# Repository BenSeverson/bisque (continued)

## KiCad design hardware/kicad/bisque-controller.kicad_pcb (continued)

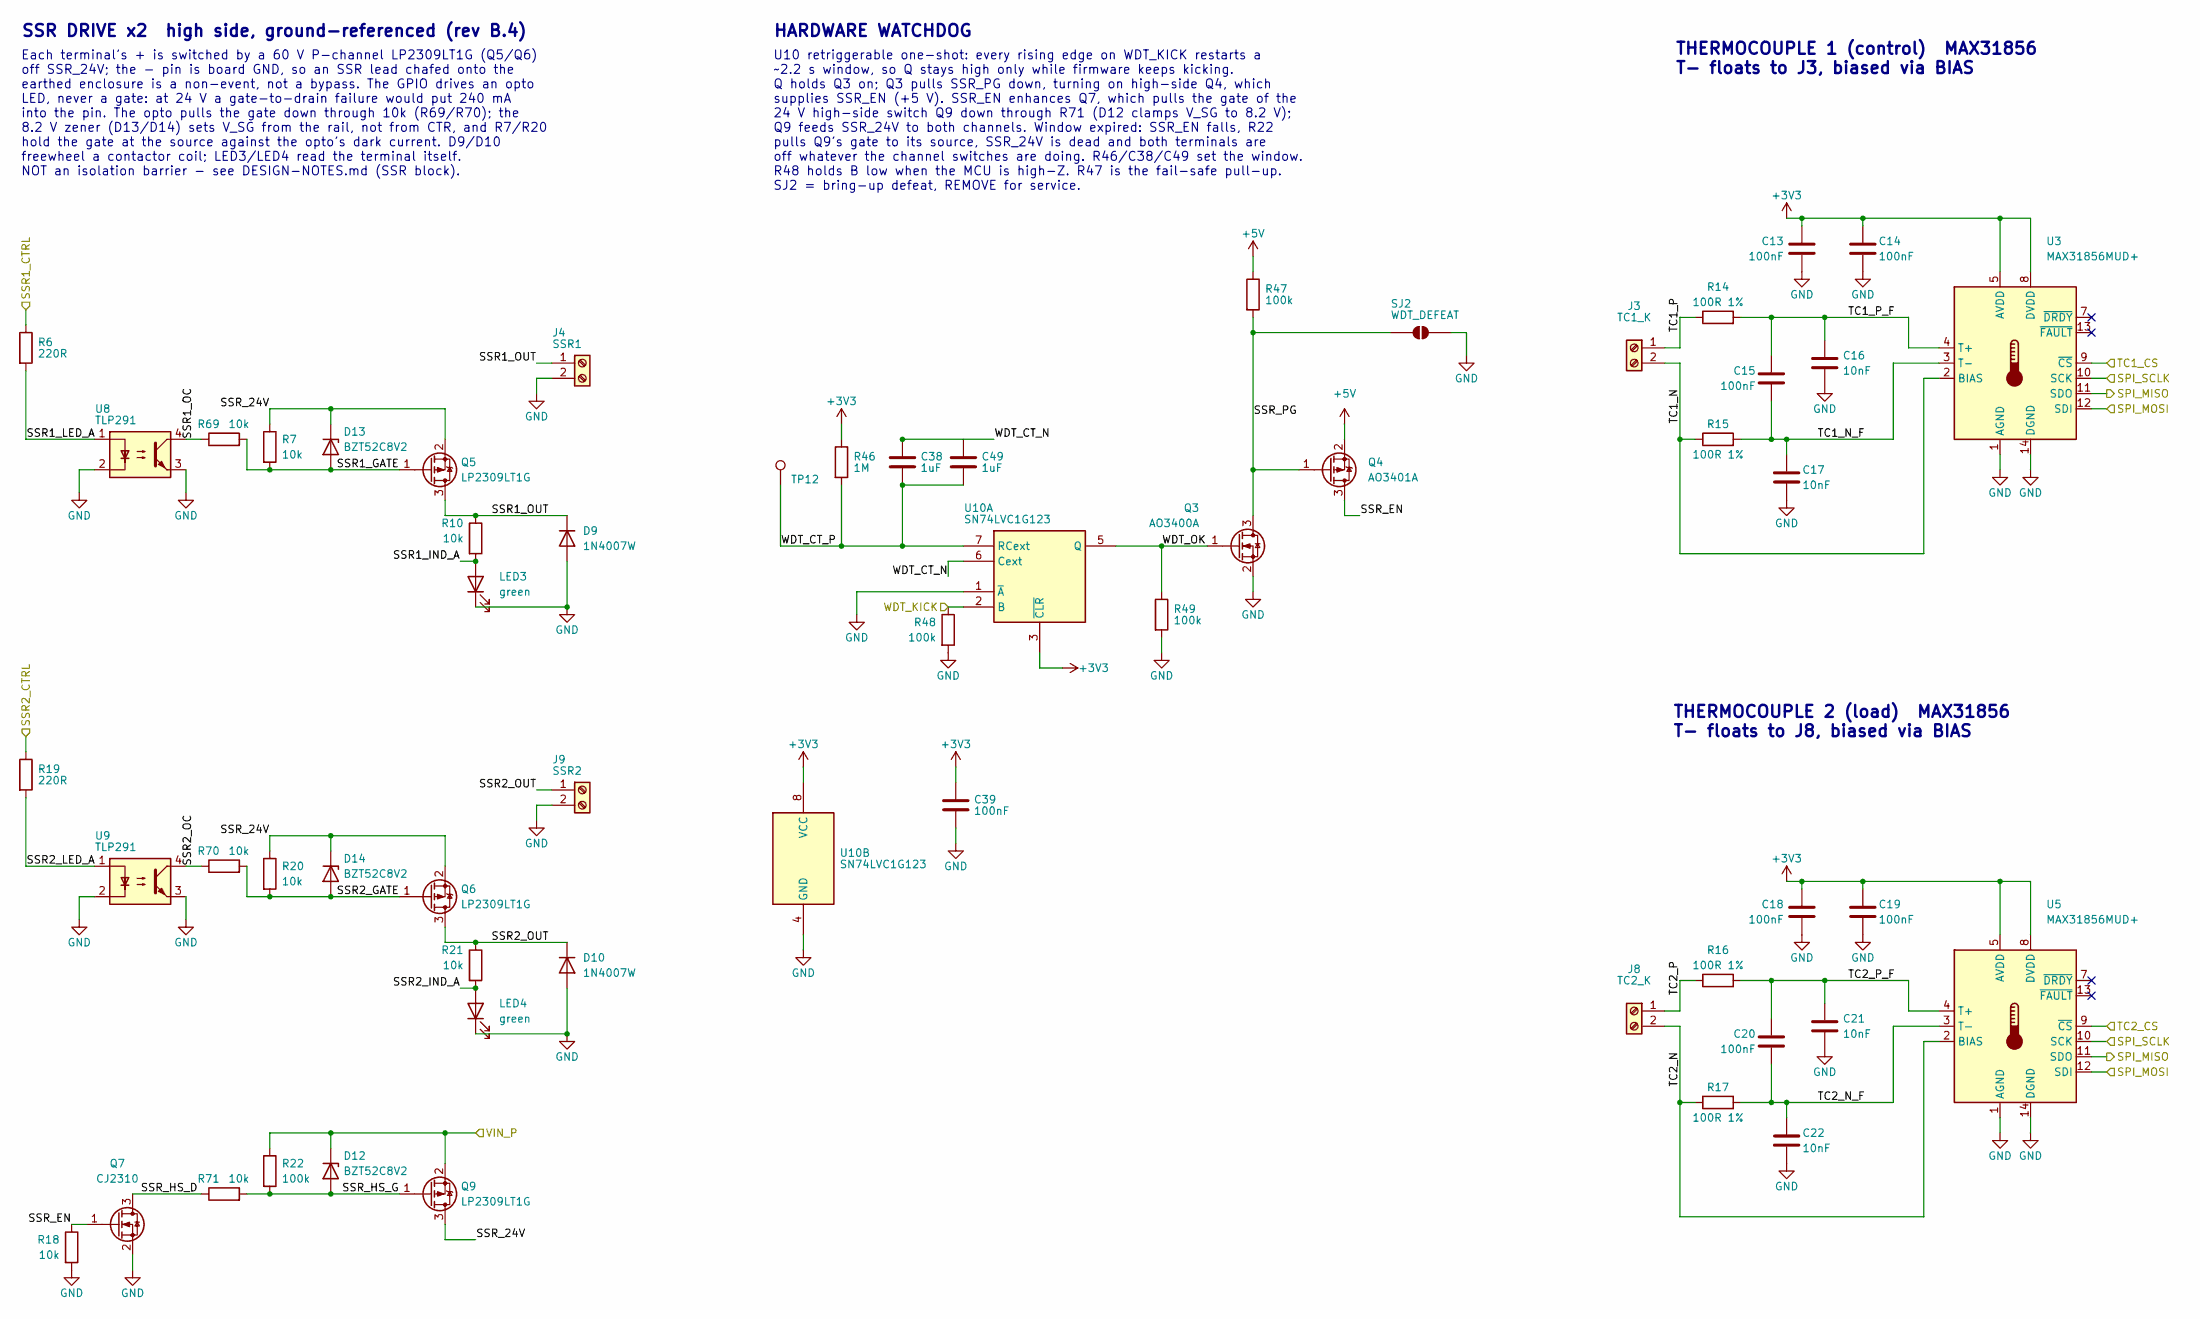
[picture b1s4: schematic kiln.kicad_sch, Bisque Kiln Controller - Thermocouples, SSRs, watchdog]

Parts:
C13, C14, C15, C18, C19, C20, C39: 100nF; C_0603_1608Metric; MPN CC0603KRX7R9BB104; LCSC C14663
C16, C17, C21, C22: 10nF; C_0805_2012Metric; MPN CL21B103KBANNNC; LCSC C1710
C38, C49: 1uF; C_0805_2012Metric; MPN CL21B105KBFNNNE; LCSC C28323
D9, D10: 1N4007W; D_SOD-123; MPN 1N4007W; LCSC C3018540
D12, D13, D14: BZT52C8V2; D_SOD-323; MPN BZT52C8V2S; LCSC C22375294
J3: TC1_K; TerminalBlock_Phoenix_MKDS-1,5-2-5.08_1x02_P5.08mm_Horizont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; MPN WJ500V-5.08-2P; LCSC C8465
J4: SSR1; TerminalBlock_Phoenix_MKDS-1,5-2-5.08_1x02_P5.08mm_Horizont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; MPN WJ500V-5.08-2P; LCSC C8465
J8: TC2_K; TerminalBlock_Phoenix_MKDS-1,5-2-5.08_1x02_P5.08mm_Horizont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; MPN WJ500V-5.08-2P; LCSC C8465
J9: SSR2; TerminalBlock_Phoenix_MKDS-1,5-2-5.08_1x02_P5.08mm_Horizont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; MPN WJ500V-5.08-2P; LCSC C8465
LED3, LED4: green; LED_0805_2012Metric; MPN KT-0805G; LCSC C2297
Q3: AO3400A; SOT-23; MPN AO3400A; LCSC C20917
Q4: AO3401A; SOT-23; MPN AO3401A; LCSC C15127
Q5, Q6, Q9: LP2309LT1G; SOT-23; MPN LP2309LT1G; LCSC C383253
Q7: CJ2310; SOT-23; MPN CJ2310; LCSC C75882
R6, R19: 220R; R_0805_2012Metric; MPN 0805W8F2200T5E; LCSC C17557
R7, R10, R18, R20, R21, R69, R70, R71: 10k; R_0805_2012Metric; MPN 0805W8F1002T5E; LCSC C17414
R14, R15, R16, R17: 100R 1%; R_0805_2012Metric; MPN 0805W8F1000T5E; LCSC C17408
R22, R47, R48, R49: 100k; R_0805_2012Metric; MPN 0805W8F1003T5E; LCSC C149504
R46: 1M; R_0805_2012Metric; MPN 0805W8F1004T5E; LCSC C17514
SJ2: WDT_DEFEAT; SolderJumper-2_P1.3mm_Open_RoundedPad1.0x1.5mm
TP12: WDT_CT_P; TestPoint_Pad_D1.0mm
U3, U5: MAX31856MUD+; TSSOP-14_4.4x5mm_P0.65mm; MPN MAX31856MUD+T; LCSC C2653162
U8, U9: TLP291; SOP-4_4.4x2.6mm_P1.27mm; MPN TLP291(GB-TP,SE; LCSC C55144
U10: SN74LVC1G123; SSOP-8_2.95x2.8mm_P0.65mm; MPN SN74LVC1G123DCTR; LCSC C123302

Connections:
+3V3: C13.1, C14.1, C18.1, C19.1, C39.1, R46.1, U3.5 (AVDD), U3.8 (DVDD), U5.5 (AVDD), U5.8 (DVDD), U10.3 (~CLR), U10.8 (VCC); also elsewhere on the board
+5V: Q4.2 (S), R47.1; also elsewhere on the board
GND: C13.2, C14.2, C16.2, C17.2, C18.2, C19.2, C21.2, C22.2, C39.2, D9.2 (A), D10.2 (A), J4.2, J9.2, LED3.1 (K), LED4.1 (K), Q3.2 (S), Q7.2 (S), R18.2, R48.2, R49.2, SJ2.2 (B), U3.1 (AGND), U3.14 (DGND), U5.1 (AGND), U5.14 (DGND), U8.2, U8.3, U9.2, U9.3, U10.1 (~A), U10.4 (GND); also elsewhere on the board
SPI_MISO: U3.11 (SDO), U5.11 (SDO); also elsewhere on the board
SPI_MOSI: U3.12 (SDI), U5.12 (SDI); also elsewhere on the board
SPI_SCLK: U3.10 (SCK), U5.10 (SCK); also elsewhere on the board
SSR1_CTRL: R6.1; also elsewhere on the board
SSR1_GATE: D13.2 (A), Q5.1 (G), R7.2, R69.2
SSR1_IND_A: LED3.2 (A), R10.2
SSR1_LED_A: R6.2, U8.1
SSR1_OC: R69.1, U8.4
SSR1_OUT: D9.1 (K), J4.1, Q5.3 (D), R10.1
SSR2_CTRL: R19.1; also elsewhere on the board
SSR2_GATE: D14.2 (A), Q6.1 (G), R20.2, R70.2
SSR2_IND_A: LED4.2 (A), R21.2
SSR2_LED_A: R19.2, U9.1
SSR2_OC: R70.1, U9.4
SSR2_OUT: D10.1 (K), J9.1, Q6.3 (D), R21.1
SSR_24V: D13.1 (K), D14.1 (K), Q5.2 (S), Q6.2 (S), Q9.3 (D), R7.1, R20.1
SSR_EN: Q4.3 (D), Q7.1 (G), R18.1
SSR_HS_D: Q7.3 (D), R71.1
SSR_HS_G: D12.2 (A), Q9.1 (G), R22.2, R71.2
SSR_PG: Q3.3 (D), Q4.1 (G), R47.2, SJ2.1 (A)
TC1_CS: U3.9 (~CS); also elsewhere on the board
TC1_N: J3.2, R15.1, U3.2 (BIAS)
TC1_N_F: C15.2, C17.1, R15.2, U3.3 (T-)
TC1_P: J3.1, R14.1
TC1_P_F: C15.1, C16.1, R14.2, U3.4 (T+)
TC2_CS: U5.9 (~CS); also elsewhere on the board
TC2_N: J8.2, R17.1, U5.2 (BIAS)
TC2_N_F: C20.2, C22.1, R17.2, U5.3 (T-)
TC2_P: J8.1, R16.1
TC2_P_F: C20.1, C21.1, R16.2, U5.4 (T+)
VIN_P: D12.1 (K), Q9.2 (S), R22.1; also elsewhere on the board
WDT_CT_N: C38.1, C49.1, U10.6 (Cext)
WDT_CT_P: C38.2, C49.2, R46.2, TP12.1, U10.7 (RCext)
WDT_KICK: R48.1, U10.2 (B); also elsewhere on the board
WDT_OK: Q3.1 (G), R49.1, U10.5 (Q)

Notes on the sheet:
SSR DRIVE x2 high side, ground-referenced (rev B.4)
Each terminal's + is switched by a 60 V P-channel LP2309LT1G (Q5/Q6) off SSR_24V; the - pin is board GND, so an SSR lead chafed onto the earthed enclosure is a non-event, not a bypass. The GPIO drives an opto LED, never a gate: at 24 V a gate-to-drain failure would put 240 mA into the pin. The opto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
HARDWARE WATCHDOG
U10 retriggerable one-shot: every rising edge on WDT_KICK restarts a ~2.2 s window, so Q stays high only while firmware keeps kicking. Q holds Q3 on; Q3 pulls SSR_PG down, turning on high-side Q4, which supplies SSR_EN (+5 V). SSR_EN enhances Q7, which pulls the gate of the 24 V high-side switch Q9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
THERMOCOUPLE 1 (control) MAX31856 T- floats to J3, biased via BIAS
THERMOCOUPLE 2 (load) MAX31856 T- floats to J8, biased via BIAS

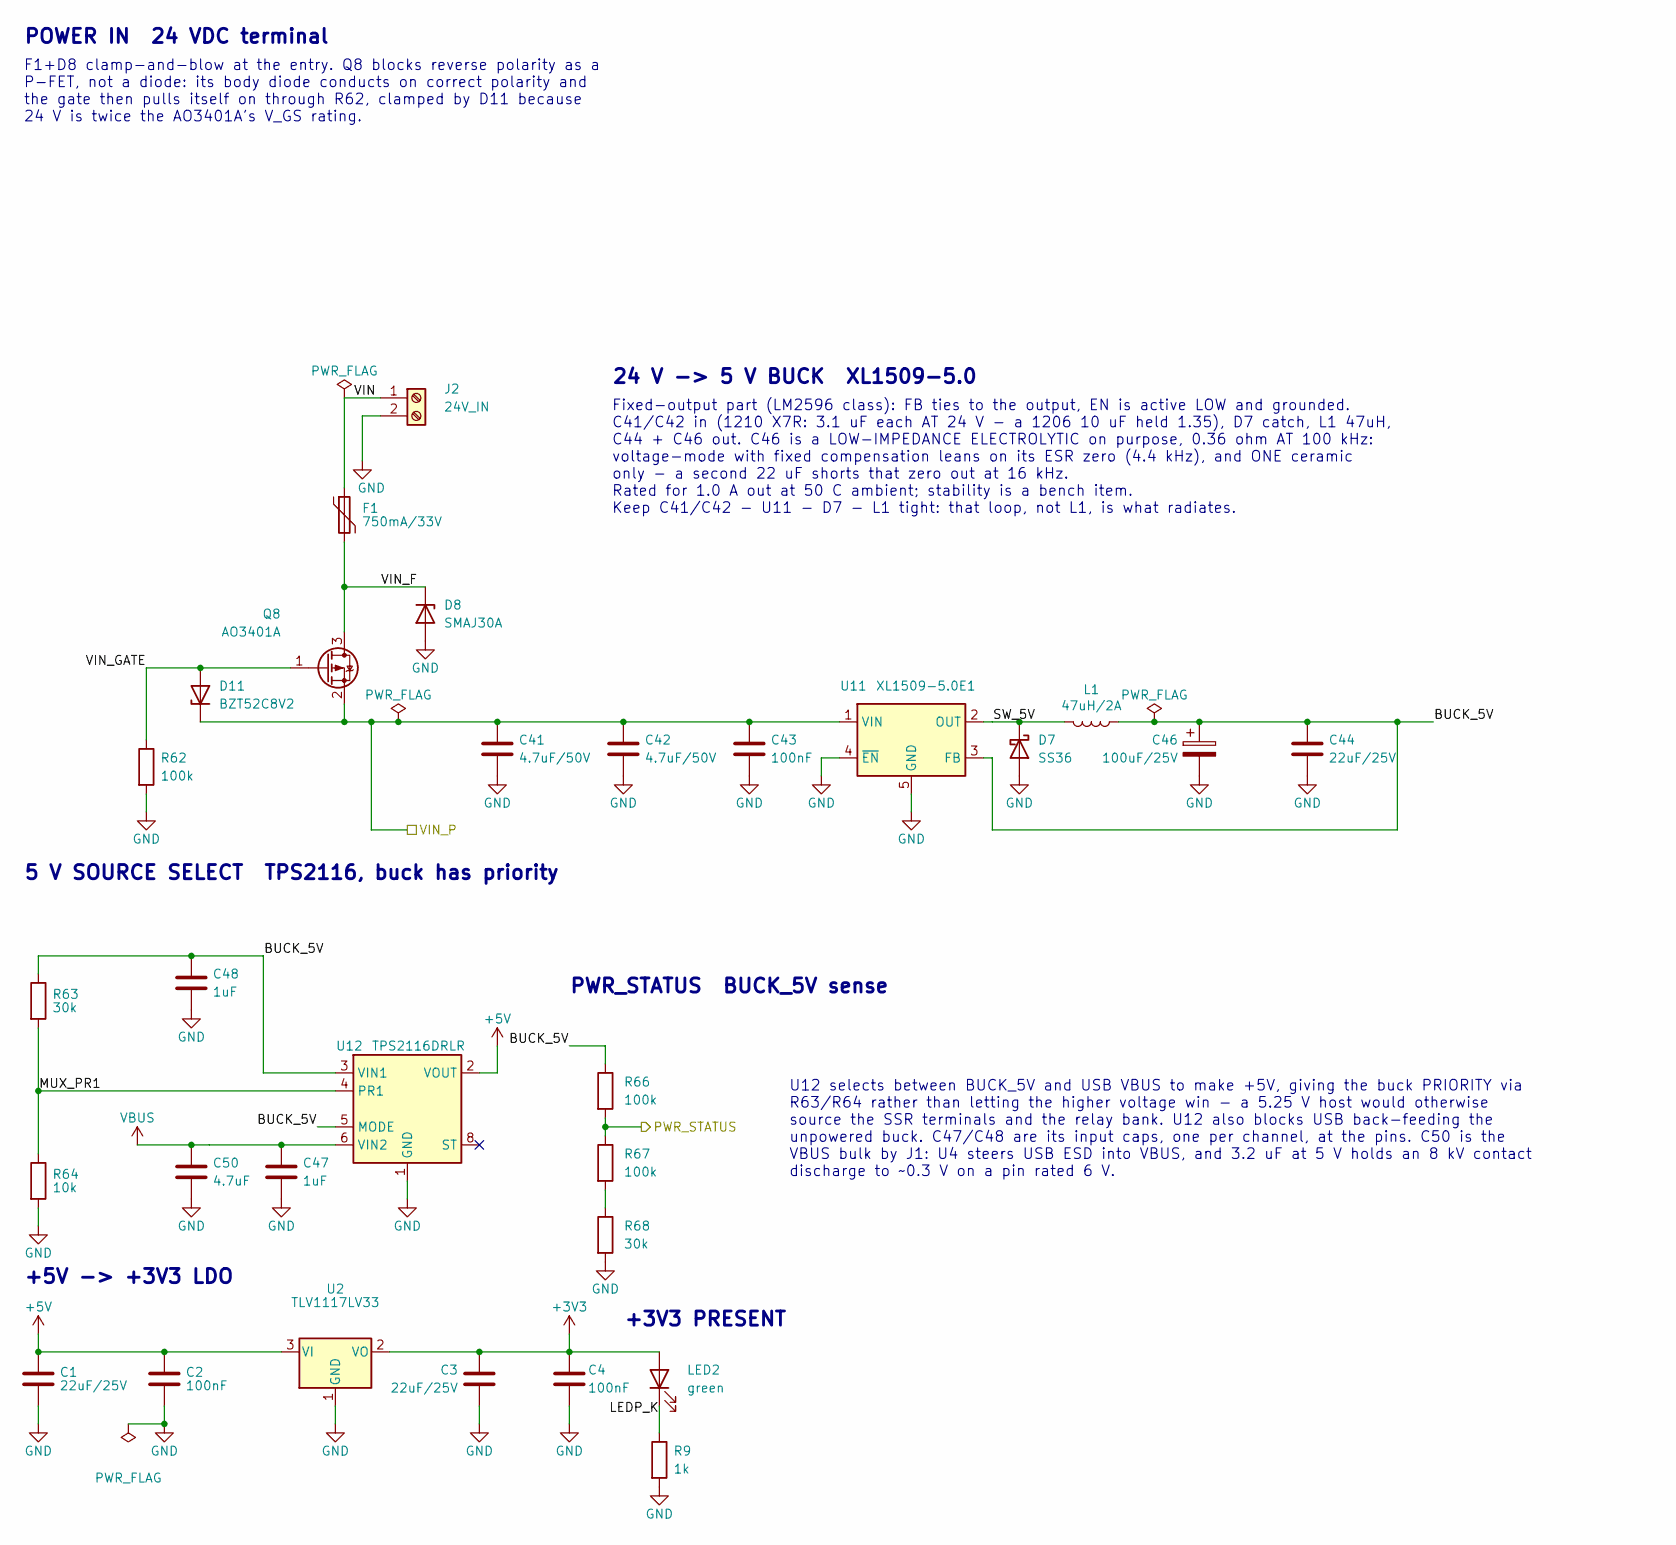
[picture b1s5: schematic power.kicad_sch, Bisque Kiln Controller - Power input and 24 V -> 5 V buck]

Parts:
C1, C3, C44: 22uF/25V; C_1206_3216Metric; MPN CL31A226KAHNNNE; LCSC C12891
C2, C4, C43: 100nF; C_0603_1608Metric; MPN CC0603KRX7R9BB104; LCSC C14663
C41, C42: 4.7uF/50V; C_1210_3225Metric; MPN CL32B475KBUYNNE; LCSC C170099
C46: 100uF/25V; CP_Elec_6.3x5.8; MPN EEEFK1E101SP; LCSC C178540
C47, C48: 1uF; C_0402_1005Metric; MPN CL05A105KA5NQNC; LCSC C52923
C50: 4.7uF; C_0805_2012Metric; MPN CL21A475KAQNNNE; LCSC C1779
D7: SS36; D_SMA; MPN SS36; LCSC C7420367
D8: SMAJ30A; D_SMA; MPN SMAJ30A; LCSC C19077547
D11: BZT52C8V2; D_SOD-323; MPN BZT52C8V2S; LCSC C22375294
F1: 750mA/33V; Fuse_1812_4532Metric; MPN JK-mSMD075-33; LCSC C369169
J2: 24V_IN; TerminalBlock_Phoenix_MKDS-1,5-2-5.08_1x02_P5.08mm_Horizont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; MPN WJ500V-5.08-2P; LCSC C8465
L1: 47uH/2A; L_Changjiang_FXL0650; MPN FXL0650-470-M; LCSC C475527
LED2: green; LED_0805_2012Metric; MPN KT-0805G; LCSC C2297
Q8: AO3401A; SOT-23; MPN AO3401A; LCSC C15127
R9: 1k; R_0805_2012Metric; MPN 0805W8F1001T5E; LCSC C17513
R62, R66, R67: 100k; R_0805_2012Metric; MPN 0805W8F1003T5E; LCSC C149504
R63, R68: 30k; R_0805_2012Metric; MPN 0805W8F3002T5E; LCSC C17621
R64: 10k; R_0805_2012Metric; MPN 0805W8F1002T5E; LCSC C17414
U2: TLV1117LV33; SOT-223-3_TabPin2; MPN TLV1117LV33DCYR; LCSC C48937499
U11: XL1509-5.0E1; SOIC-8_3.9x4.9mm_P1.27mm; MPN XL1509-5.0E1; LCSC C61063
U12: TPS2116DRLR; SOT-583-8; MPN TPS2116DRLR; LCSC C3235557

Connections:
+3V3: C3.1, C4.1, LED2.2 (A), U2.2 (VO); also elsewhere on the board
+5V: C1.1, C2.1, U2.3 (VI), U12.2 (VOUT), U12.7 (VOUT); also elsewhere on the board
BUCK_5V: C44.1, C46.1, C48.1, L1.1, R63.1, R66.1, U11.3 (FB), U12.3 (VIN1), U12.5 (MODE)
GND: C1.2, C2.2, C3.2, C4.2, C41.2, C42.2, C43.2, C44.2, C46.2, C47.2, C48.2, C50.2, D7.2 (A), D8.2 (A), J2.2, R9.2, R62.2, R64.2, R68.2, U2.1 (GND), U11.4 (~EN), U11.5 (GND), U11.6 (GND), U11.7 (GND), U11.8 (GND), U12.1 (GND); also elsewhere on the board
LEDP_K: LED2.1 (K), R9.1
MUX_PR1: R63.2, R64.1, U12.4 (PR1)
unnamed: R67.2, R68.1
PWR_STATUS: R66.2, R67.1; also elsewhere on the board
SW_5V: D7.1 (K), L1.2, U11.2 (OUT)
VBUS: C47.1, C50.1, U12.6 (VIN2); also elsewhere on the board
VIN: F1.1, J2.1
VIN_F: D8.1 (K), F1.2, Q8.3 (D)
VIN_GATE: D11.2 (A), Q8.1 (G), R62.1
VIN_P: C41.1, C42.1, C43.1, D11.1 (K), Q8.2 (S), U11.1 (VIN); also elsewhere on the board

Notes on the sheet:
POWER IN 24 VDC terminal
F1+D8 clamp-and-blow at the entry. Q8 blocks reverse polarity as a P-FET, not a diode: its body diode conducts on correct polarity and the gate then pulls itself on through R62, clamped by D11 because 24 V is twice the AO3401A's V_GS rating.
24 V -> 5 V BUCK XL1509-5.0
Fixed-output part (LM2596 class): FB ties to the output, EN is active LOW and grounded. C41/C42 in (1210 X7R: 3.1 uF each AT 24 V - a 1206 10 uF held 1.35), D7 catch, L1 47uH, C44 + C46 out. C46 is a LOW-IMPEDANCE ELECTROLYTIC on purpose, 0.36 ohm AT 100 kHz: voltage-mode with fixed compensation le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
5 V SOURCE SELECT TPS2116, buck has priority
PWR_STATUS BUCK_5V sense
+3V3 PRESENT
+5V -> +3V3 LDO
U12 selects between BUCK_5V and USB VBUS to make +5V, giving the buck PRIORITY via R63/R64 rather than letting the higher voltage win - a 5.25 V host would otherwise source the SSR terminals and the relay bank. U12 also blocks USB back-feeding the unpowered buck. C47/C48 are its input caps, one per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

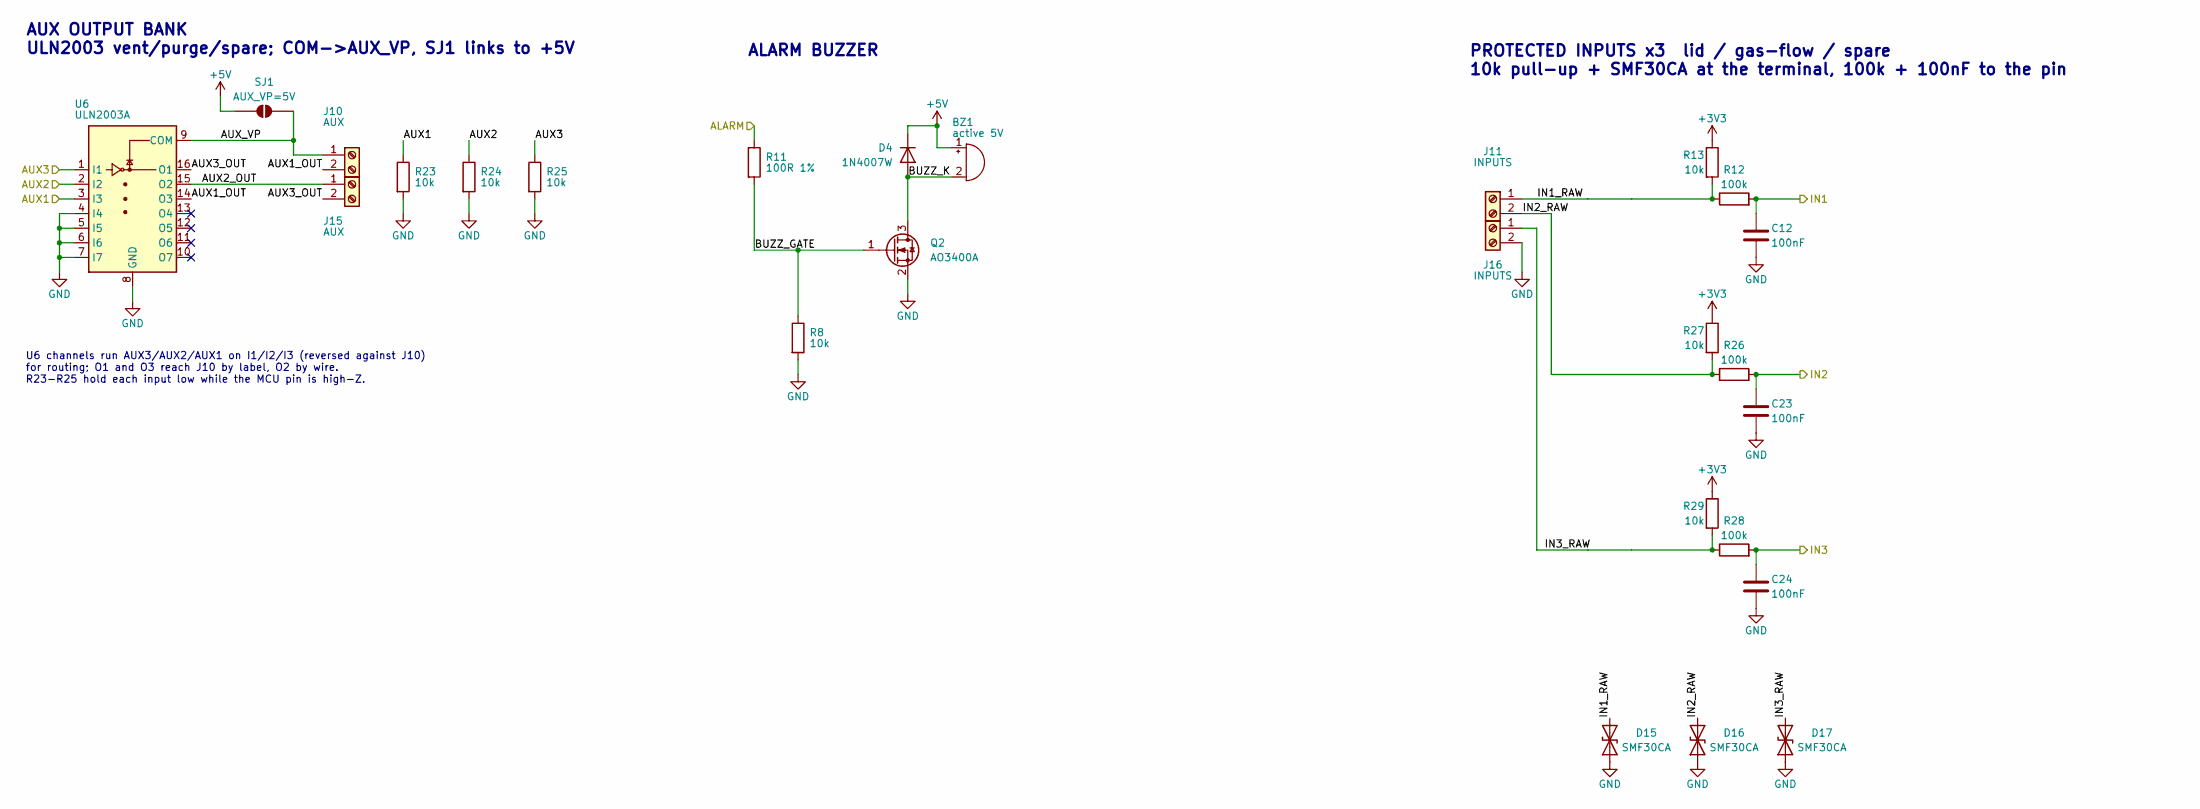
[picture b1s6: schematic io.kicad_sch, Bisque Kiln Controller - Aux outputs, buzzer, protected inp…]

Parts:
BZ1: active 5V; Buzzer_12x9.5RM7.6; MPN TMB12A05; LCSC C96093
C12, C23, C24: 100nF; C_0603_1608Metric; MPN CC0603KRX7R9BB104; LCSC C14663
D4: 1N4007W; D_SOD-123; MPN 1N4007W; LCSC C3018540
D15, D16, D17: SMF30CA; D_SOD-123F; MPN SMF30CA; LCSC C2943771
J10, J15: AUX; TerminalBlock_Phoenix_MKDS-1,5-2-5.08_1x02_P5.08mm_Horizont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; MPN WJ500V-5.08-2P; LCSC C8465
J11, J16: INPUTS; TerminalBlock_Phoenix_MKDS-1,5-2-5.08_1x02_P5.08mm_Horizont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; MPN WJ500V-5.08-2P; LCSC C8465
Q2: AO3400A; SOT-23; MPN AO3400A; LCSC C20917
R8, R13, R23, R24, R25, R27, R29: 10k; R_0805_2012Metric; MPN 0805W8F1002T5E; LCSC C17414
R11: 100R 1%; R_0805_2012Metric; MPN 0805W8F1000T5E; LCSC C17408
R12, R26, R28: 100k; R_0805_2012Metric; MPN 0805W8F1003T5E; LCSC C149504
SJ1: AUX_VP=5V; SolderJumper-2_P1.3mm_Open_RoundedPad1.0x1.5mm
U6: ULN2003A; SOIC-16_3.9x9.9mm_P1.27mm; MPN ULN2003ADR; LCSC C7512

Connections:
+3V3: R13.1, R27.1, R29.1; also elsewhere on the board
+5V: BZ1.1 (+), D4.1 (K), SJ1.1 (A); also elsewhere on the board
ALARM: R11.1; also elsewhere on the board
AUX1: R23.1, U6.3 (I3); also elsewhere on the board
AUX1_OUT: J10.2, U6.14 (O3)
AUX2: R24.1, U6.2 (I2); also elsewhere on the board
AUX2_OUT: J15.1, U6.15 (O2)
AUX3: R25.1, U6.1 (I1); also elsewhere on the board
AUX3_OUT: J15.2, U6.16 (O1)
AUX_VP: J10.1, SJ1.2 (B), U6.9 (COM)
BUZZ_GATE: Q2.1 (G), R8.1, R11.2
BUZZ_K: BZ1.2 (-), D4.2 (A), Q2.3 (D)
GND: C12.2, C23.2, C24.2, D15.1 (A1), D16.1 (A1), D17.1 (A1), J16.2, Q2.2 (S), R8.2, R23.2, R24.2, R25.2, U6.4 (I4), U6.5 (I5), U6.6 (I6), U6.7 (I7), U6.8 (GND); also elsewhere on the board
IN1: C12.1, R12.2; also elsewhere on the board
IN1_RAW: D15.2 (A2), J11.1, R12.1, R13.2
IN2: C23.1, R26.2; also elsewhere on the board
IN2_RAW: D16.2 (A2), J11.2, R26.1, R27.2
IN3: C24.1, R28.2; also elsewhere on the board
IN3_RAW: D17.2 (A2), J16.1, R28.1, R29.2

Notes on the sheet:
ALARM BUZZER
PROTECTED INPUTS x3 lid / gas-flow / spare 10k pull-up + SMF30CA at the terminal, 100k + 100nF to the pin
U6 channels run AUX3/AUX2/AUX1 on I1/I2/I3 (reversed against J10) for routing; O1 and O3 reach J10 by label, O2 by wire. R23-R25 hold each input low while the MCU pin is high-Z.
AUX OUTPUT BANK ULN2003 vent/purge/spare; COM->AUX_VP, SJ1 links to +5V

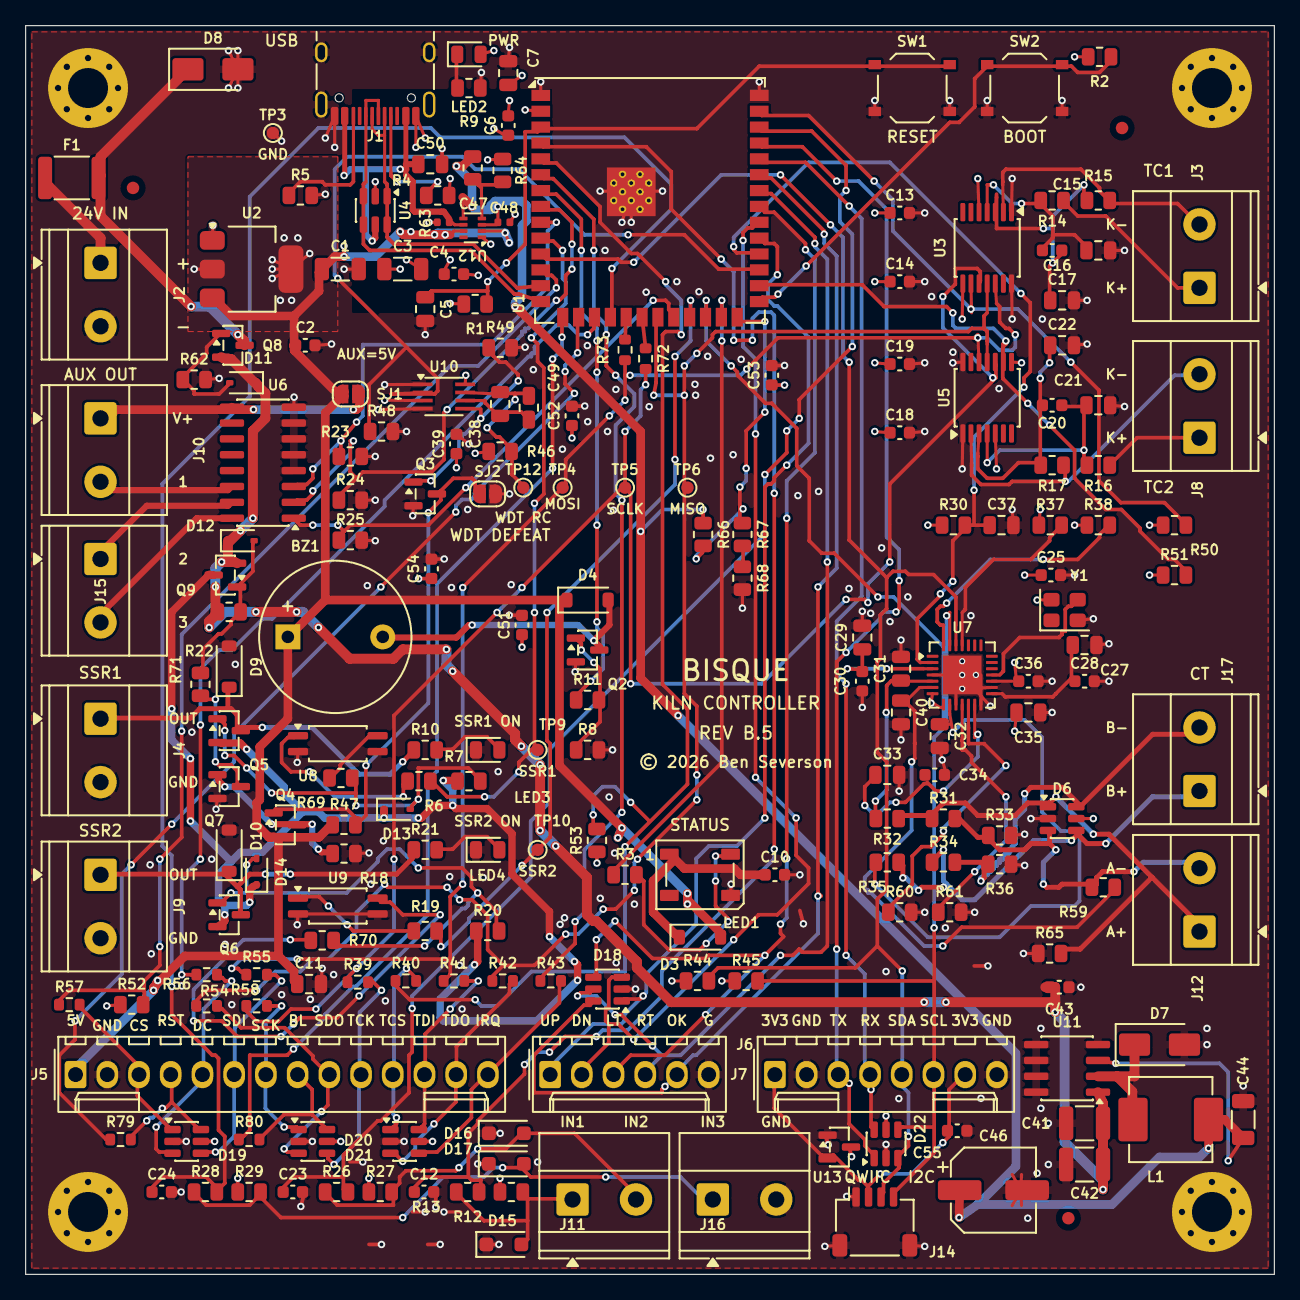
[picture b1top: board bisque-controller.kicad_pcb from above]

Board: 4 copper layers, 100.0 x 100.0 mm, 208 parts (0 on the bottom side), 119 nets.

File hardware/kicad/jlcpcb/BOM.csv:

"Comment","Designator","Footprint","LCSC Part #","MPN","Manufacturer","Qty","Notes"
"active 5V","BZ1","Buzzer_12x9.5RM7.6","C96093","TMB12A05","Huaneng","1","Optional hand solder - JLC assembles; untick at JLC to fit by hand"
"22uF/25V","C1,C3,C44","C_1206_3216Metric","C12891","CL31A226KAHNNNE","Samsung Electro-Mechanics","3",""
"100nF","C2,C4,C6,C10,C12,C13,C14,C15,C18,C19,C20,C23,C24,C25,C28,C30,C34,C36,C39,C43,C51,C52,C53,C54,C55","C_0603_1608Metric","C14663","CC0603KRX7R9BB104","YAGEO","25",""
"1uF","C5,C37,C38,C49","C_0805_2012Metric","C28323","CL21B105KBFNNNE","Samsung Electro-Mechanics","4",""
"10uF","C7,C11,C35","C_0805_2012Metric","C15850","CL21A106KAYNNNE","Samsung Electro-Mechanics","3",""
"10nF","C16,C17,C21,C22","C_0805_2012Metric","C1710","CL21B103KBANNNC","Samsung Electro-Mechanics","4",""
"4.7uF","C27,C29,C33,C50","C_0805_2012Metric","C1779","CL21A475KAQNNNE","Samsung Electro-Mechanics","4",""
"33nF","C31,C32,C40","C_0805_2012Metric","C1739","0805B333K500NT","FH","3",""
"4.7uF/50V","C41,C42","C_1210_3225Metric","C170099","CL32B475KBUYNNE","Samsung Electro-Mechanics","2",""
"100uF/25V","C46","CP_Elec_6.3x5.8","C178540","EEEFK1E101SP","PANASONIC","1",""
"1uF","C47,C48","C_0402_1005Metric","C52923","CL05A105KA5NQNC","Samsung Electro-Mechanics","2",""
"1N4007W","D3,D4,D9,D10","D_SOD-123","C3018540","1N4007W","FUXINSEMI","4",""
"SRV05-4","D6,D19,D20,D21,D22,U4","SOT-23-6","C7420376","SRV05-4","R+O","6",""
"SS36","D7","D_SMA","C7420367","SS36","R+O","1",""
"SMAJ30A","D8","D_SMA","C19077547","SMAJ30A","R+O","1",""
"BZT52C8V2","D11,D12,D13,D14","D_SOD-323","C22375294","BZT52C8V2S","R+O","4",""
"SMF30CA","D15,D16,D17","D_SOD-123F","C2943771","SMF30CA","GOODWORK","3",""
"ESDA6V1-5SC6","D18","SOT-23-6","C2827672","ESDA6V1-5SC6","TECH PUBLIC","1",""
"750mA/33V","F1","Fuse_1812_4532Metric","C369169","JK-mSMD075-33","Jinrui","1",""
"USB-C","J1","USB_C_Receptacle_HRO_TYPE-C-31-M-12","C165948","TYPE-C-31-M-12","Korean Hroparts Elec","1",""
"24V_IN,AUX,CT,INPUTS,SSR1,SSR2,TC1_K,TC2_K","J2,J3,J4,J8,J9,J10,J11,J12,J15,J16,J17","TerminalBlock_Phoenix_MKDS-1,5-2-5.08_1x02_P5.08mm_Horizontal","C8465","WJ500V-5.08-2P","KANGNEX","11","Optional hand solder - JLC assembles; untick at JLC to fit by hand"
"DISPLAY","J5","Molex_KK-254_AE-6410-14A_1x14_P2.54mm_Vertical","C17701004","XD-2510-14A","chxunda","1","Optional hand solder - JLC assembles; untick at JLC to fit by hand"
"NAV_SW","J6","Molex_KK-254_AE-6410-06A_1x06_P2.54mm_Vertical","C239381","A2547WV-6P","CJT(Changjiang Connectors)","1","Optional hand solder - JLC assembles; untick at JLC to fit by hand"
"AUX","J7","Molex_KK-254_AE-6410-08A_1x08_P2.54mm_Vertical","C240822","22272081","MOLEX","1","Optional hand solder - JLC assembles; untick at JLC to fit by hand"
"QWIIC","J14","JST_SH_SM04B-SRSS-TB_1x04-1MP_P1.00mm_Horizontal","C160404","SM04B-SRSS-TB(LF)(SN)","JST","1",""
"47uH/2A","L1","L_Changjiang_FXL0650","C475527","FXL0650-470-M","cjiang","1",""
"WS2812B","LED1","LED_WS2812B_PLCC4_5.0x5.0mm_P3.2mm","C2920042","WS2812E-V5","Worldsemi","1","Optional hand solder - JLC assembles; untick at JLC to fit by hand"
"green","LED2,LED3,LED4","LED_0805_2012Metric","C2297","KT-0805G","Hubei KENTO Elec","3",""
"AO3400A","Q2,Q3","SOT-23","C20917","AO3400A","AOS","2",""
"AO3401A","Q4,Q8","SOT-23","C15127","AO3401A","AOS","2",""
"LP2309LT1G","Q5,Q6,Q9","SOT-23","C383253","LP2309LT1G","LRC","3",""
"CJ2310","Q7","SOT-23","C75882","CJ2310","JSCJ","1",""
"10k","R1,R2,R7,R8,R10,R13,R18,R20,R21,R23,R24,R25,R27,R29,R30,R37,R38,R50,R51,R52,R53,R64,R69,R70,R71","R_0805_2012Metric","C17414","0805W8F1002T5E","UNI-ROYAL","25",""
"220R","R3,R6,R19","R_0805_2012Metric","C17557","0805W8F2200T5E","UNI-ROYAL","3",""
"5.1k","R4,R5,R44,R45","R_0805_2012Metric","C27834","0805W8F5101T5E","UNI-ROYAL","4",""
"1k","R9,R32,R33,R35,R36,R59,R60,R61,R65","R_0805_2012Metric","C17513","0805W8F1001T5E","UNI-ROYAL","9",""
"100R 1%","R11,R14,R15,R16,R17","R_0805_2012Metric","C17408","0805W8F1000T5E","UNI-ROYAL","5",""
"100k","R12,R22,R26,R28,R47,R48,R49,R62,R66,R67","R_0805_2012Metric","C149504","0805W8F1003T5E","UNI-ROYAL","10",""
"5R1","R31,R34","R_0805_2012Metric","C17724","0805W8F510KT5E","UNI-ROYAL","2",""
"33","R39,R40,R41,R42,R43,R54,R55,R56,R57,R58,R72,R73,R79,R80","R_0603_1608Metric","C23140","0603WAF330JT5E","UNI-ROYAL","14",""
"1M","R46","R_0805_2012Metric","C17514","0805W8F1004T5E","UNI-ROYAL","1",""
"30k","R63,R68","R_0805_2012Metric","C17621","0805W8F3002T5E","UNI-ROYAL","2",""
"BOOT,RESET","SW1,SW2","SW_Push_1P1T_XKB_TS-1187A","C318884","TS-1187A-B-A-B","XKB Connection","2",""
"ESP32-S3-WROOM-1U-N16R2","U1","ESP32-S3-WROOM-1U","C3013945","ESP32-S3-WROOM-1U-N16R2","ESPRESSIF","1",""
"TLV1117LV33","U2","SOT-223-3_TabPin2","C48937499","TLV1117LV33DCYR","JSMSEMI","1",""
"MAX31856MUD+","U3,U5","TSSOP-14_4.4x5mm_P0.65mm","C2653162","MAX31856MUD+T","MAXIM","2",""
"ULN2003A","U6","SOIC-16_3.9x9.9mm_P1.27mm","C7512","ULN2003ADR","TI","1",""
"ADE7953ACPZ","U7","QFN-28-1EP_5x5mm_P0.5mm_EP3.1x3.1mm","C515890","ADE7953ACPZ-RL","ADI","1",""
"TLP291","U8,U9","SOP-4_4.4x2.6mm_P1.27mm","C55144","TLP291(GB-TP,SE","TOSHIBA","2",""
"SN74LVC1G123","U10","SSOP-8_2.95x2.8mm_P0.65mm","C123302","SN74LVC1G123DCTR","TI","1",""
"XL1509-5.0E1","U11","SOIC-8_3.9x4.9mm_P1.27mm","C61063","XL1509-5.0E1","XLSEMI","1",""
"TPS2116DRLR","U12","SOT-583-8","C3235557","TPS2116DRLR","TI","1",""
"AP2331SA-7","U13","SOT-23","C500764","AP2331SA-7","DIODES","1",""
"3.579545MHz XO","Y1","Oscillator_SMD_Abracon_ASE-4Pin_3.2x2.5mm","C2838127","TFOM3.579545M4RHKCNT2T","Yajingxin","1",""

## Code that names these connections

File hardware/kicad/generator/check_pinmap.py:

#!/usr/bin/env python3
"""Assert the GPIO map agrees across the three places allowed to state it.

The schematic (via the committed netlist, bisque-controller.net) owns which
GPIO the board wires to each net; main/Kconfig.projbuild owns each pin's
firmware default; docs/pin-assignments.md §1 is the one table written for
people. Nothing else in the repo restates a GPIO number. This checks all three
against each other, so a re-map that updates one and forgets another fails
loudly instead of reaching a fab house - or a reader.

Module pin number -> GPIO for ESP32-S3-WROOM-1 / -1U (identical pinout).
"""
import os
import re
import sys

sys.path.insert(0, os.path.dirname(__file__))
import netlist as NL

NETLIST = os.path.join(os.path.dirname(os.path.abspath(__file__)), os.pardir,
                       "bisque-controller.net")

REPO = os.path.normpath(os.path.join(os.path.dirname(__file__), "..", "..", ".."))
KCONFIG = os.path.join(REPO, "main", "Kconfig.projbuild")
PIN_DOC = os.path.join(REPO, "docs", "pin-assignments.md")

# U1 module pin -> GPIO number. From the ESP32-S3-WROOM-1 datasheet pad list;
# the 1U is identical. Pins carrying power, EN or GND are absent.
MODULE_PIN_GPIO = {
    4: 4, 5: 5, 6: 6, 7: 7, 8: 15, 9: 16, 10: 17, 11: 18, 12: 8,
    13: 19, 14: 20, 15: 3, 16: 46, 17: 9, 18: 10, 19: 11, 20: 12,
    21: 13, 22: 14, 23: 21, 24: 47, 25: 48, 26: 45, 27: 0,
    28: 35, 29: 36, 30: 37, 31: 38, 32: 39, 33: 40, 34: 41, 35: 42,
    36: 44, 37: 43, 38: 2, 39: 1,
}

# Nets on U1 that are fixed-function and correctly have NO Kconfig pin symbol:
# the native USB peripheral (GPIO 19/20), the UART0 console (GPIO 43/44) and
# the BOOT strapping pin (GPIO 0). These must never count as unmapped.
NO_KCONFIG_SYMBOL = {"USB_DN", "USB_DP", "TXD0", "RXD0", "IO0"}

# net name -> Kconfig symbol that must hold that GPIO.
NET_KCONFIG = {
    # SCLK/MOSI leave U1 through series resistors R72/R73 (PCB review
    # 2026-10-05 item 5): the pin-side stub is the *_U1 net, the bus beyond the
    # resistor keeps the plain name. The GPIO is on the stub.
    "SPI_MOSI_U1": "KILN_PIN_SPI_MOSI",
    "SPI_MISO": "KILN_PIN_SPI_MISO",
    "SPI_SCLK_U1": "KILN_PIN_SPI_SCLK",
    "TC1_CS": "KILN_PIN_TC1_CS",
    "TC2_CS": "KILN_PIN_TC2_CS",
    "SSR1_CTRL": "KILN_PIN_SSR1",
    "SSR2_CTRL": "KILN_PIN_SSR2",
    "LCD_CS": "KILN_PIN_LCD_CS",
    "LCD_DC": "KILN_PIN_LCD_DC",
    "LCD_RST": "KILN_PIN_LCD_RST",
    "LCD_BL": "KILN_PIN_LCD_BL",
    "LED_DATA": "KILN_PIN_STATUS_LED",
    "ALARM": "KILN_PIN_ALARM",
    "AUX1": "KILN_PIN_VENT",
    "AUX2": "KILN_PIN_AUX2",
    "AUX3": "KILN_PIN_AUX3",
    "IN1": "KILN_PIN_LID_SWITCH",
    "IN2": "KILN_PIN_IN_GASFLOW",
    "IN3": "KILN_PIN_IN_SPARE",
    "I2C_SDA": "KILN_PIN_I2C_SDA",
    "I2C_SCL": "KILN_PIN_I2C_SCL",
    "T_CS": "KILN_PIN_TOUCH_CS",
    "T_IRQ": "KILN_PIN_TOUCH_IRQ",
    "WDT_KICK": "KILN_PIN_WDT_KICK",
    "BTN_UP": "KILN_PIN_BTN_UP",
    "BTN_DOWN": "KILN_PIN_BTN_DOWN",
    "BTN_LEFT": "KILN_PIN_BTN_LEFT",
    "BTN_RIGHT": "KILN_PIN_BTN_RIGHT",
    "BTN_SEL": "KILN_PIN_BTN_SELECT",
    "ADE_RESET": "KILN_PIN_ADE_RESET",
    "PWR_STATUS": "KILN_PIN_PWR_STATUS",
}


def kconfig_defaults(path):
    """{symbol: int default} for every `config X` / `default N` int option."""
    out, sym = {}, None
    for line in open(path):
        m = re.match(r"\s*config\s+(\w+)\s*$", line)
        if m:
            sym = m.group(1)
            continue
        m = re.match(r"\s*default\s+(-?\d+)\s*$", line)
        if m and sym:
            out.setdefault(sym, int(m.group(1)))
    return out


def u1_pins():
    """{module pin: net or None} for U1, from the committed netlist."""
    return {int(pin): net for pin, net in NL.load(NETLIST).comps["U1"]["pins"].items()}


def board_gpios():
    """{net: gpio} for every U1 pin that carries a mapped signal."""
    out = {}
    for pin, net in u1_pins().items():
        gpio = MODULE_PIN_GPIO.get(pin)
        if net is not None and gpio is not None:
            out[net] = gpio
    return out


def doc_rows(path):
    """[(gpio, module pin, net or None, kconfig symbol or None, line)] from the
    first table in docs/pin-assignments.md whose header starts `| GPIO | Module pin |`."""
    rows, in_table = [], False
    for line in open(path, encoding="utf-8"):
        cells = [c.strip() for c in line.strip().strip("|").split("|")]
        if not in_table:
            in_table = cells[:2] == ["GPIO", "Module pin"]
            continue
        if not line.startswith("|"):
            break
        if set(cells[0]) <= set("-: "):
            continue
        dash = lambda c: None if c in ("—", "-", "") else c.strip("`")
        rows.append((int(cells[0]), int(cells[1]), dash(cells[3]), dash(cells[5]),
                     line.rstrip()))
    return rows


def check_doc(path, pins):
    """Errors where docs/pin-assignments.md §1 disagrees with the netlist or NET_KCONFIG."""
    errors, seen = [], set()
    rows = doc_rows(path)
    if not rows:
        return ["%s: no `| GPIO | Module pin |` table found" % path]
    for gpio, mpin, net, sym, line in rows:
        where = "%s GPIO %d" % (os.path.basename(path), gpio)
        if MODULE_PIN_GPIO.get(mpin) != gpio:
            errors.append("%s: module pin %d is GPIO %s, not %d"
                          % (where, mpin, MODULE_PIN_GPIO.get(mpin), gpio))
        if pins.get(mpin) != net:
            errors.append("%s: table says net %s, the schematic wires U1 pin %d to %s"
                          % (where, net, mpin, pins.get(mpin)))
        want = NET_KCONFIG.get(net)
        if sym != want:
            errors.append("%s: table names Kconfig %s for net %s, expected %s"
                          % (where, sym, net, want))
        seen.add(mpin)
    missing = sorted(p for p, g in MODULE_PIN_GPIO.items() if p not in seen)
    if missing:
        errors.append("%s: no row for U1 pin(s) %s"
                      % (os.path.basename(path), ", ".join(map(str, missing))))
    return errors


def main():
    defaults = kconfig_defaults(KCONFIG)
    board = board_gpios()
    errors = []

    for net, sym in NET_KCONFIG.items():
        on_board = board.get(net)
        in_kconfig = defaults.get(sym)
        if on_board is None:
            errors.append("net %s is in NET_KCONFIG but not on U1 in the schematic" % net)
        elif in_kconfig is None:
            errors.append("%s has no integer default in Kconfig.projbuild" % sym)
        elif on_board != in_kconfig:
            errors.append("%s: Kconfig says GPIO %d, the schematic wires net %s to GPIO %d"
                          % (sym, in_kconfig, net, on_board))

    unmapped = sorted(set(board) - set(NET_KCONFIG) - NO_KCONFIG_SYMBOL)
    if unmapped:
        errors.append("U1 nets with no Kconfig symbol: %s" % ", ".join(unmapped))

    errors += check_doc(PIN_DOC, u1_pins())

    if errors:
        for e in errors:
            print("FAIL: %s" % e)
        return 1
    print("check_pinmap: %d GPIO assignments agree between Kconfig, the schematic "
          "and docs/pin-assignments.md" % len(NET_KCONFIG))
    return 0


if __name__ == "__main__":
    sys.exit(main())
